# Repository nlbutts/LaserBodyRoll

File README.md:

# LaserBodyRoll

This product is designed to simulate wheel slip to prevent the front of a car from rising off the ground during hard acceleration. The device would be connected in between a wheel speed sensor and an engine ECU. Under normal conditions the device would pass through the wheel speed sensor directly to the engine ECU. If the front of the vehicle is detected rising off the ground, the system would increase the number of pulses per second (PPS) of the wheel to the engine ECU to simulate wheel slip. In theory, this should cause the engine ECU to reduce timing to prevent the simulated wheel slip and therefore reduce the front end from rising off the ground.
The system detects front end rise by using a laser rangefinder. The laser rangefinder can detect the small changes in distance from the mounting location to the ground. If the distance is increasing, then the system can increase the number of PPS from the wheel speed sensor to simulate the slip.

# Hardware Connections
A single cable gland will be used to bring signals into and out of the ECU enclosure.

ECU Connector

| Wire   | Description   |
| ------ | -----------   |
| Purple  | Power        |
| Black  | Ground        |
| Grey   | Analog Out 1  |
| Red    | Analog Out 2  |
| Brown  | DIN           |
| Orange | DOUT          |
| Yellow | CAN High      |
| Green  | CAN Low       |

The goal is to fit into this 

# Protocol between Processor and BLE
The PSoC and the Raspberry PI are connected via an SPI bus. The Pi is the SPI Master and the PSoC is a slave device. The packet that is transmitted to the PSOC is shown below

| Sync1 (8) | Sync2 (8) | Version (4)/Msg ID (4) | Length (8) | payload (2040) | CRC (8) |
| --------- | --------- | ---------------------- | ---------- | -------------- | ------- |
| 0x55      | 0xAA      | 0x01 / MSG ID          |            |                |         |

The number in parenthesis is how many bits are used for the various fields
The 4-bits of the version allows updates to the protocol. The 4-bits for the message ID allows
128 different message IDs. Length is the number of bytes in the payload 0-255 bytes.
The CRC is the CRC-8-CCITT using the following generator polynominal:
x^8 + x^2 + x + 1 (0x7)

| MSG ID | Description |
| ------ | ------------|
| 0      | Data input  |
| 1      | Data output |
| 2      | Main programming image |
| 3      | BLE programming image  |

Data input is a generic pass through message from the BLE interface to the main processor. The
data input is made up of an 8-bit UUID followed by the data item. Each data item has a unique
length, format, scale, etc. Data output is the same as data input, just going in the other
direction

| UUID | Description             | Size (bytes) | Data type | Units |
| ---- | ----------------------- | ------------ | --------- | ----- |
| 0    | Analog 1 slope          | 4            | float     | mm/mv |
| 1    | Analog 1 y offset       | 4            | float     | mv    |
| 2    | Analog 2 slope          | 4            | float     | mm/mv |
| 3    | Analog 2 y offset       | 4            | float     | mv    |
| 4    | Open drain pull up enbl | 1            | uint8     | bool  |
| 5    | Laser distance in mm    | 2            | uint16    | mm    |
| 6    | Accel X in mg           | 2            | uint16    | mg    |
| 7    | Accel Y in mg           | 2            | uint16    | mg    |
| 8    | Accel Z in mg           | 2            | uint16    | mg    |
| 9    | Gyro X in dps           | 2            | uint16    | dps   |
| 10   | Gyro Y in dps           | 2            | uint16    | dps   |
| 11   | Gyro Z in dps           | 2            | uint16    | dps   |
| 12   | Auto level gain         | 4            | float     |       |
| 13   | EPOCH time              | 4            | uint32    | epoch |
| 14   | Super cap voltage       | 2            | uint32    | mv    |

The main programming image is a LZMA compressed binary file. The BLE programming
image is an LZMA compressed cyacd file. Each BLE packet is only 23 bytes or so.
The programming images are transmitted with a byte counter as the first byte
of the payload. This allows a check that a packet hasn't been dropped and they are being
received in the correct order.

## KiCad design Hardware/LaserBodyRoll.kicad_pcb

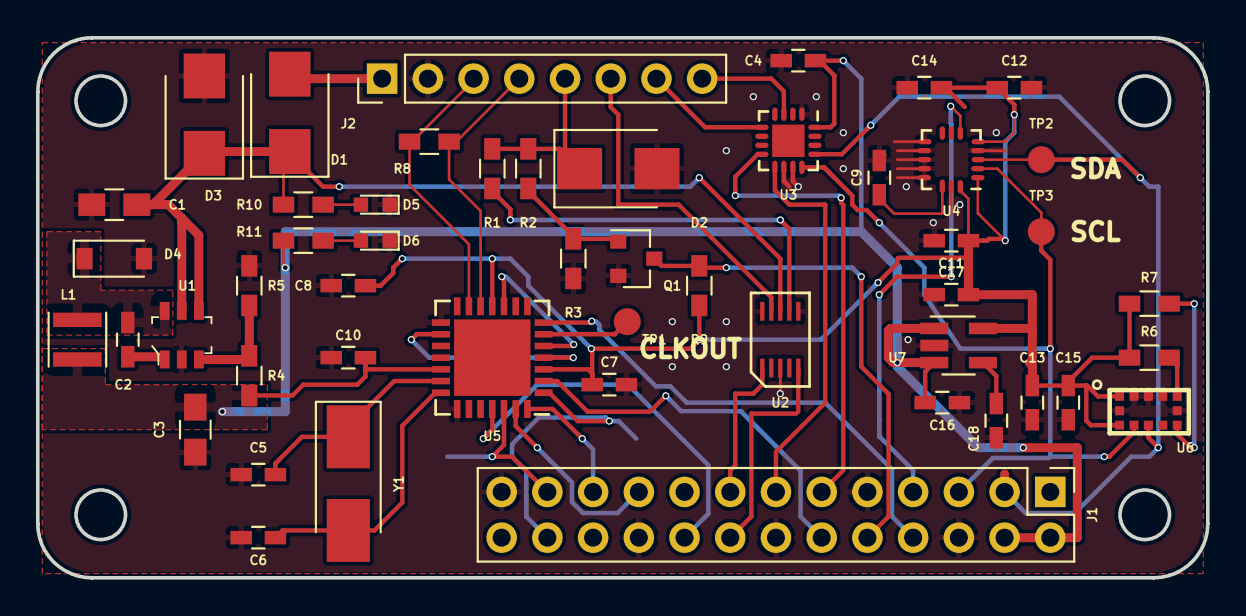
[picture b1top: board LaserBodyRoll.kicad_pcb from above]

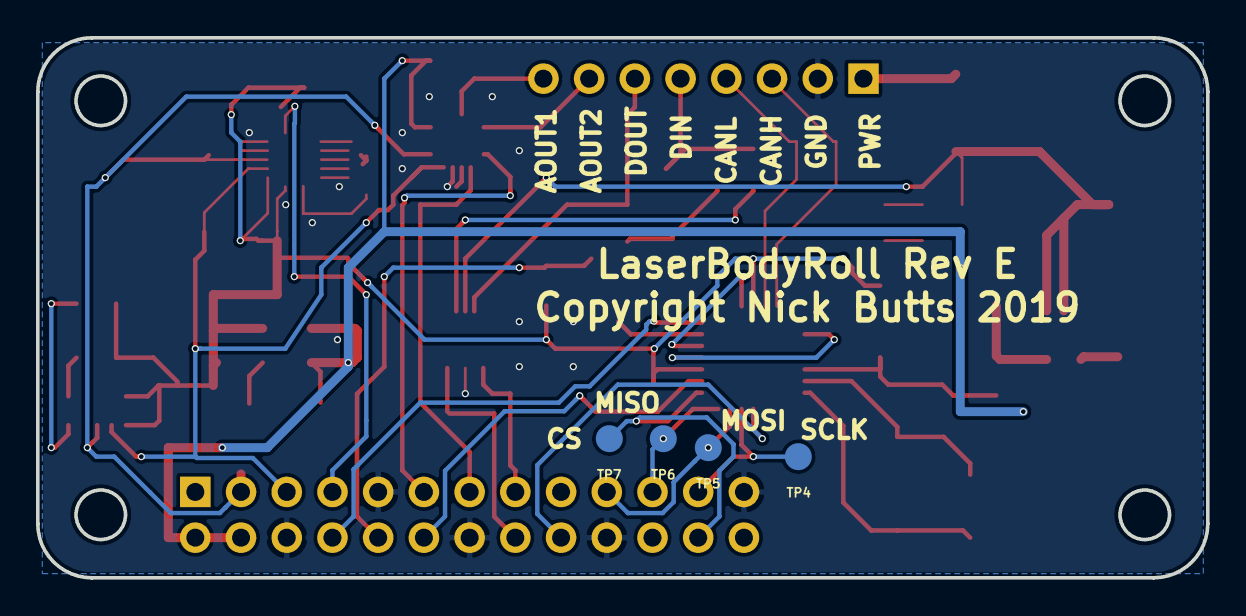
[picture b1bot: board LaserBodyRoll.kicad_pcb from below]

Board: 2 copper layers, 65.0 x 30.0 mm, 54 parts (4 on the bottom side), 42 nets.

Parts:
C1, C3: 10u; C_0805_HandSoldering
C2, C14: 10n; C_0603_HandSoldering
C4, C7, C8, C9, C10, C11, C13, C16, C18: 0.1u; C_0603_HandSoldering
C5, C6: 22p; C_0603_HandSoldering
C12: 2.2U; C_0603_HandSoldering
C15: 4.7u; C_0603_HandSoldering
C17: 1u; C_0603_HandSoldering
D1: STPS2L40; D_SMB
D2, D3: D_TVS; D_SMB
D4: D_Schottky; D_SOD-123
D5, D6: LED; LED_0603
J1: Conn_02x13_Odd_Even; Pin_Header_Straight_2x13_Pitch2.54mm
J2: Conn_01x08; Pin_Header_Straight_1x08_Pitch2.54mm
L1: 4.7u; L_Taiyo-Yuden_MD-3030
Q1: Q_NPN_BCE; SOT-23
R1, R2, R3: 24.3k; R_0603_HandSoldering
R4: 49.9k; R_0603_HandSoldering
R5: 9.53k; R_0603_HandSoldering
R6, R7: 10k; R_0603_HandSoldering
R8: 120; R_0603_HandSoldering
R9: 1k; R_0603_HandSoldering
R10: 600; R_0603_HandSoldering
R11: 250; R_0603_HandSoldering
TP1, TP2, TP3, TP4, TP5, TP6, TP7: TestPoint; Measurement_Point_Round-SMD-Pad_Small
U1: AOZ1280CI; SOT-23-6
U2: ITS42K5D; PG-TSON-10
U3: MCP47X; QFN-16-1EP_3x3mm_Pitch0.5mm
U4: ICM-20602; QFN-16-no_center_3x3mm_Pitch0.5mm
U5: MCP25625; QFN-28-1EP_6x6mm_Pitch0.65mm
U6: VL53L0X; VL53L0x
U7: LD3985; SOT-23-5_HandSoldering
Y1: 16MHz; Crystal_SMD_5032-2pin_5.0x3.2mm_HandSoldering

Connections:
12V: C1.1, D1.1, D3.1, R10.1, U1.4, U1.5, U2.8
+5V: C3.1, C4.1, C10.2, C16.2, J1.2, J1.4, L1.2, R4.1, R11.1, U3.16, U5.19, U7.1, U7.3
/12V_PULLUP: R1.2, U2.7
/ANA_OUT1: J2.8, U3.3
/ANA_OUT2: J2.7, U3.5
/CANH: J2.3, R8.1, U5.13
/CANL: J2.4, R8.2, U5.12
/DIN: D2.1, J2.5, R1.1, R2.1
/DOUT: J2.6, U2.9
/VL53L0X_GP: R7.2, U6.7
/VL53L0X_XSHUT: R6.2, U6.5
BCM4: J1.7, U4.6
BCM14: J1.8, U5.7
BCM15: J1.10, Q1.3, R9.2
BCM17: J1.11, U3.8
BCM18: J1.12, U5.2
BCM22: J1.15, U2.1
BCM23: J1.16, U2.5
BCM24: J1.18, U5.25
BCM27: J1.13, U3.9
GND: C1.2, C3.2, C4.2, C5.2, C6.2, C7.2, C8.2, C9.2, C10.1, C11.2, C12.2, C13.2, C14.2, C15.2, C16.1, C17.1, C18.1, D2.2, D3.2, D4.2, D5.1, D6.1, J1.6, J1.9, J1.14, J1.20, J1.25, J2.2, Q1.2, R3.2, R5.2, U1.2, U2.3, U2.6, U2.10, U3.1, U3.10, U3.11, U4.4, U4.9, U4.10, U4.11, U4.12, U4.13, U4.15, U5.15, U5.18, U5.22, U6.2, U6.3, U6.4, U6.6, U6.12, U7.2
unnamed: C2.1, D4.1, L1.1, U1.6
unnamed: C2.2, U1.1
unnamed: C5.1, U5.20, Y1.1
unnamed: C6.1, U5.21, Y1.2
unnamed: C9.1, U4.14
unnamed: C18.2, U7.4
unnamed: D5.2, R10.2
unnamed: D6.2, R11.2
unnamed: Q1.1, R2.2, R3.1
unnamed: R4.2, R5.1, U1.3
unnamed: TP1.1, U5.6
unnamed: U5.5, U5.10
unnamed: U5.4, U5.16
PI_CLK: J1.23, TP4.1, U5.26
PI_MISO: J1.21, TP6.1, U5.28
PI_MOSI: J1.19, TP5.1, U5.27
PI_NSS: J1.24, TP7.1, U5.1
SCL: J1.5, TP3.1, U3.12, U4.2, U6.10
SDA: J1.3, TP2.1, U3.13, U4.3, U6.9
VCC: C7.1, C8.1, C11.1, C12.1, C13.1, C14.1, C15.1, C17.2, R6.1, R7.1, R9.1, U4.1, U4.5, U4.16, U5.3, U5.11, U6.1, U6.11, U7.5
VIN: D1.2, J2.1

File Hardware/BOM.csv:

Source:,C:\projects\LaserBodyRoll\Hardware\LaserBodyRoll.sch,,,,,,,,,,,,,,,,
Date:,3/24/2019 14:10,,,,,,,,,,,,,,,,
Tool:,Eeschema (5.1.0)-1,,,,,,,,,,,,,,,,
Generator:,C:\Program Files\KiCad\bin\scripting\plugins/bom_csv_grouped_by_value.py,,,,,,,,,,,,,,,,
Component Count:,42,,,,,,,,,,,,,,,,
,,,,,,,,,,,,,,,,,
Individual Components:,,,,,,,,,,,,,,,,,
,,,,,,,,,,,,,,,,,
Item,Qty,Reference(s),Value,LibPart,Footprint,Datasheet,Category,DK_Datasheet_Link,DK_Detail_Page,Description,Digi-Key_PN,Digikey,Family,MPN,Manufacturer,Partnum,Status
,,C1,10u,Device:C,Capacitors_SMD:C_0805_HandSoldering,,,,,,,490-5523-1-ND,,,,GRM21BR61E106KA73L,
,,C2,10n,Device:C,Capacitors_SMD:C_0603_HandSoldering,,,,,,,399-1092-1-ND,,,,C0603C103J5RACTU,
,,C3,10u,Device:C,Capacitors_SMD:C_0805_HandSoldering,,,,,,,490-5523-1-ND,,,,GRM21BR61E106KA73L,
,,C4,0.1u,Device:C,Capacitors_SMD:C_0603_HandSoldering,~,,,,,,,,,,,
,,C5,22p,Device:C,Capacitors_SMD:C_0603_HandSoldering,~,,,,,,,,,,,
,,C6,22p,Device:C,Capacitors_SMD:C_0603_HandSoldering,~,,,,,,,,,,,
,,C7,0.1u,Device:C,Capacitors_SMD:C_0603_HandSoldering,~,,,,,,,,,,,
,,C8,0.1u,Device:C,Capacitors_SMD:C_0603_HandSoldering,~,,,,,,,,,,,
,,C9,0.1u,Device:C,Capacitors_SMD:C_0603_HandSoldering,,,,,,,,,,,,
,,C10,0.1u,Device:C,Capacitors_SMD:C_0603_HandSoldering,~,,,,,,,,,,,
,,C11,0.1u,Device:C,Capacitors_SMD:C_0603_HandSoldering,,,,,,,,,,,,
,,C12,2.2U,Device:C,Capacitors_SMD:C_0603_HandSoldering,,,,,,,,,,,,
,,C13,0.1u,Device:C,Capacitors_SMD:C_0603_HandSoldering,,,,,,,,,,,,
,,C14,10n,Device:C,Capacitors_SMD:C_0603_HandSoldering,,,,,,,,,,,,
,,C15,4.7u,Device:C,Capacitors_SMD:C_0603_HandSoldering,,,,,,,,,,,,
,,C16,0.1u,Device:C,Capacitors_SMD:C_0603_HandSoldering,~,,,,,,,,,,,
,,C17,0.1u,Device:C,Capacitors_SMD:C_0603_HandSoldering,~,,,,,,,,,,,
,,D1,STPS2L40,Device:D,Diodes_SMD:D_SMB,,,,,,,497-5574-1-ND,,,,STPS2L40U,
,,D2,D_TVS,Device:D_TVS,Diodes_SMD:D_SMB,,,,,,,732-9779-1-ND,,,,824520201,
,,D3,D_TVS,Device:D_TVS,Diodes_SMD:D_SMB,,,,,,,732-9779-1-ND,,,,824520201,
,,D4,D_Schottky,Device:D_Schottky,Diodes_SMD:D_SOD-123,,,,,,,B0540W-FDICT-ND,,,,B0540W-7-F,
,,J1,Conn_02x13_Odd_Even,Connector_Generic:Conn_02x13_Odd_Even,Pin_Headers:Pin_Header_Straight_2x13_Pitch2.54mm,~,,,,,,,,,,,
,,J2,Conn_01x08,Connector_Generic:Conn_01x08,Pin_Headers:Pin_Header_Straight_1x08_Pitch2.54mm,~,,,,,,,,,,,
,,L1,4.7u,Device:L,Inductors_SMD:L_Taiyo-Yuden_MD-3030,,,,,,,490-15954-1-ND,,,,LQH3NPN4R7MMEL,
,,Q1,Q_NPN_BCE,Device:Q_NPN_BCE,TO_SOT_Packages_SMD:SOT-23,,,,,,,MMBT3904FSCT-ND,,,,,
,,R1,24.3k,Device:R,Resistors_SMD:R_0603_HandSoldering,,,,,,,,,,,,
,,R2,24.3k,Device:R,Resistors_SMD:R_0603_HandSoldering,,,,,,,,,,,,
,,R3,24.3k,Device:R,Resistors_SMD:R_0603_HandSoldering,,,,,,,,,,,,
,,R4,49.9k,Device:R,Resistors_SMD:R_0603_HandSoldering,,,,,,,,,,,,
,,R5,9.53k,Device:R,Resistors_SMD:R_0603_HandSoldering,,,,,,,,,,,,
,,R6,10k,Device:R,Resistors_SMD:R_0603_HandSoldering,,,,,,,,,,,,
,,R7,10k,Device:R,Resistors_SMD:R_0603_HandSoldering,,,,,,,,,,,,
,,R8,120,Device:R,Resistors_SMD:R_0603_HandSoldering,~,,,,,,,,,,,
,,R9,1k,Device:R,Resistors_SMD:R_0603_HandSoldering,~,,,,,,,,,,,
,,U1,AOZ1280CI,dk_PMIC-Voltage-Regulators-DC-DC-Switching-Regulators:AOZ1280CI,digikey-footprints:SOT-23-6,http://aosmd.com/res/data_sheets/AOZ1280CI.pdf,Integrated Circuits (ICs),http://aosmd.com/res/data_sheets/AOZ1280CI.pdf,/product-detail/en/alpha-omega-semiconductor-inc/AOZ1280CI/785-1277-1-ND/2769845,IC REG BUCK ADJ 1.2A SOT23-6,785-1277-1-ND,,PMIC - Voltage Regulators - DC DC Switching Regulators,AOZ1280CI,Alpha & Omega Semiconductor Inc.,,Active
,,U2,ITS42K5D,General:ITS42K5D,KicadFootprint:PG-TSON-10,,,,,,,ITS42K5DLDFXUMA1CT-ND,,,,ITS42K5DLDFXUMA1,
,,U3,MCP47X,General:MCP47X,Housings_DFN_QFN:QFN-16-1EP_3x3mm_Pitch0.5mm,,,,,,,MCP47CVB22-E/MG-ND,,,,,
,,U4,ICM-20602,General:ICM-20602,Housings_DFN_QFN:QFN-16-1EP_3x3mm_Pitch0.5mm,,,,,,,1428-1060-1-ND,,,,ICM-20602,
,,U5,MCP25625,General:MCP25625,Housings_DFN_QFN:QFN-28-1EP_6x6mm_Pitch0.65mm,,,,,,,MCP25625T-E/MLCT-ND,,,,,
,,U6,VL53L0X,General:VL53L0X,KicadFootprint:VL53L0x,,,,,,,"	497-16538-1-ND",,,,VL53L0CXV0DH/1,
,,U7,LD3985,General:LD3985,TO_SOT_Packages_SMD:SOT-23-5_HandSoldering,,,,,,,497-3504-1-ND,,,,,
,,Y1,16MHz,Device:Crystal,Crystals:Crystal_SMD_5032-2pin_5.0x3.2mm_HandSoldering,~,,,,,,,,,,,
,,,,,,,,,,,,,,,,,
,,,,,,,,,,,,,,,,,
,,,,,,,,,,,,,,,,,
Collated Components:,,,,,,,,,,,,,,,,,
,,,,,,,,,,,,,,,,,
Item,Qty,Reference(s),Value,LibPart,Footprint,Datasheet,Category,DK_Datasheet_Link,DK_Detail_Page,Description,Digi-Key_PN,Digikey,Family,MPN,Manufacturer,Partnum,Status
1,2,"C1, C3",10u,Device:C,Capacitors_SMD:C_0805_HandSoldering,,,,,,,490-5523-1-ND,,,,GRM21BR61E106KA73L,
2,2,"C2, C14",10n,Device:C,Capacitors_SMD:C_0603_HandSoldering,,,,,,,399-1092-1-ND,,,,C0603C103J5RACTU,
3,9,"C4, C7, C8, C9, C10, C11, C13, C16, C17",0.1u,Device:C,Capacitors_SMD:C_0603_HandSoldering,~,,,,,,,,,,,
4,2,"C5, C6",22p,Device:C,Capacitors_SMD:C_0603_HandSoldering,~,,,,,,,,,,,
5,1,C12,2.2U,Device:C,Capacitors_SMD:C_0603_HandSoldering,,,,,,,,,,,,
6,1,C15,4.7u,Device:C,Capacitors_SMD:C_0603_HandSoldering,,,,,,,,,,,,
7,1,D1,STPS2L40,Device:D,Diodes_SMD:D_SMB,,,,,,,497-5574-1-ND,,,,STPS2L40U,
8,2,"D2, D3",D_TVS,Device:D_TVS,Diodes_SMD:D_SMB,,,,,,,732-9779-1-ND,,,,824520201,
9,1,D4,D_Schottky,Device:D_Schottky,Diodes_SMD:D_SOD-123,,,,,,,B0540W-FDICT-ND,,,,B0540W-7-F,
10,1,J1,Conn_02x13_Odd_Even,Connector_Generic:Conn_02x13_Odd_Even,Pin_Headers:Pin_Header_Straight_2x13_Pitch2.54mm,~,,,,,,,,,,,
11,1,J2,Conn_01x08,Connector_Generic:Conn_01x08,Pin_Headers:Pin_Header_Straight_1x08_Pitch2.54mm,~,,,,,,,,,,,
12,1,L1,4.7u,Device:L,Inductors_SMD:L_Taiyo-Yuden_MD-3030,,,,,,,490-15954-1-ND,,,,LQH3NPN4R7MMEL,
13,1,Q1,Q_NPN_BCE,Device:Q_NPN_BCE,TO_SOT_Packages_SMD:SOT-23,,,,,,,MMBT3904FSCT-ND,,,,,
14,3,"R1, R2, R3",24.3k,Device:R,Resistors_SMD:R_0603_HandSoldering,,,,,,,,,,,,
15,1,R4,49.9k,Device:R,Resistors_SMD:R_0603_HandSoldering,,,,,,,,,,,,
16,1,R5,9.53k,Device:R,Resistors_SMD:R_0603_HandSoldering,,,,,,,,,,,,
17,2,"R6, R7",10k,Device:R,Resistors_SMD:R_0603_HandSoldering,,,,,,,,,,,,
18,1,R8,120,Device:R,Resistors_SMD:R_0603_HandSoldering,~,,,,,,,,,,,
19,1,R9,1k,Device:R,Resistors_SMD:R_0603_HandSoldering,~,,,,,,,,,,,
20,1,U1,AOZ1280CI,dk_PMIC-Voltage-Regulators-DC-DC-Switching-Regulators:AOZ1280CI,digikey-footprints:SOT-23-6,http://aosmd.com/res/data_sheets/AOZ1280CI.pdf,Integrated Circuits (ICs),http://aosmd.com/res/data_sheets/AOZ1280CI.pdf,/product-detail/en/alpha-omega-semiconductor-inc/AOZ1280CI/785-1277-1-ND/2769845,IC REG BUCK ADJ 1.2A SOT23-6,785-1277-1-ND,,PMIC - Voltage Regulators - DC DC Switching Regulators,AOZ1280CI,Alpha & Omega Semiconductor Inc.,,Active
21,1,U2,ITS42K5D,General:ITS42K5D,KicadFootprint:PG-TSON-10,,,,,,,ITS42K5DLDFXUMA1CT-ND,,,,ITS42K5DLDFXUMA1,
22,1,U3,MCP47X,General:MCP47X,Housings_DFN_QFN:QFN-16-1EP_3x3mm_Pitch0.5mm,,,,,,,MCP47CVB22-E/MG-ND,,,,,
23,1,U4,ICM-20602,General:ICM-20602,Housings_DFN_QFN:QFN-16-1EP_3x3mm_Pitch0.5mm,,,,,,,1428-1060-1-ND,,,,ICM-20602,
24,1,U5,MCP25625,General:MCP25625,Housings_DFN_QFN:QFN-28-1EP_6x6mm_Pitch0.65mm,,,,,,,MCP25625T-E/MLCT-ND,,,,,
25,1,U6,VL53L0X,General:VL53L0X,KicadFootprint:VL53L0x,,,,,,,"	497-16538-1-ND",,,,VL53L0CXV0DH/1,
26,1,U7,LD3985,General:LD3985,TO_SOT_Packages_SMD:SOT-23-5_HandSoldering,,,,,,,497-3504-1-ND,,,,,
27,1,Y1,16MHz,Device:Crystal,Crystals:Crystal_SMD_5032-2pin_5.0x3.2mm_HandSoldering,~,,,,,,,,,,,

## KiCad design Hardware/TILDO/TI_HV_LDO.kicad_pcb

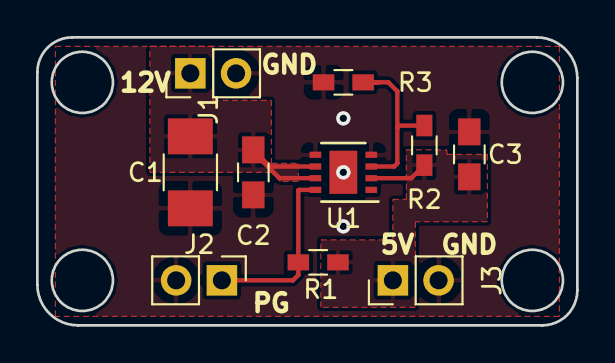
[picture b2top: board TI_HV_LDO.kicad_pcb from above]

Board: 2 copper layers, 30.0 x 16.0 mm, 10 parts (0 on the bottom side), 5 nets.

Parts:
C1: 22u; C_1210_HandSoldering
C2, C3: 10u; C_0805_HandSoldering
J1, J2, J3: Conn_01x02; Pin_Header_Straight_1x02_Pitch2.54mm
R1, R3: 10k; R_0603_HandSoldering
R2: 30k; R_0603_HandSoldering
U1: TPS7A19; DFN-8-1EP_3x3mm_Pitch0.65mm

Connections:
GND: C1.2, C2.2, C3.2, J1.2, J2.2, J3.2, R3.2, U1.4, U1.5, U1.9
unnamed: C1.1, C2.1, J1.1, U1.6, U1.7
unnamed: C3.1, J3.1, R1.2, R2.1, U1.2
unnamed: J2.1, R1.1, U1.8
unnamed: R2.2, R3.1, U1.3

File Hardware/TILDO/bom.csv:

"Source:","C:\projects\LaserBodyRoll\Hardware\TILDO\TI_HV_LDO.sch"
"Date:","6/24/2018 4:46:14 PM"
"Tool:","Eeschema (2017-09-19 revision dddaa7e69)-makepkg"
"Generator:","bom_csv_grouped_by_value.py"
"Component Count:","10"

"Individual Components:"

"Item","Qty","Reference(s)","Value","LibPart","Footprint","Datasheet"
"","","C1","22u","device:C","Capacitors_SMD:C_1210_HandSoldering",""
"","","C2","10u","device:C","Capacitors_SMD:C_0805_HandSoldering",""
"","","C3","10u","device:C","Capacitors_SMD:C_0805_HandSoldering",""
"","","J1","Conn_01x02","conn:Conn_01x02","Pin_Headers:Pin_Header_Straight_1x02_Pitch2.54mm",""
"","","J2","Conn_01x02","conn:Conn_01x02","Pin_Headers:Pin_Header_Straight_1x02_Pitch2.54mm",""
"","","J3","Conn_01x02","conn:Conn_01x02","Pin_Headers:Pin_Header_Straight_1x02_Pitch2.54mm",""
"","","R1","10k","device:R","Resistors_SMD:R_0603_HandSoldering",""
"","","R2","30k","device:R","Resistors_SMD:R_0603_HandSoldering",""
"","","R3","10k","device:R","Resistors_SMD:R_0603_HandSoldering",""
"","","U1","TPS7A19","General:TPS7A19","Housings_DFN_QFN:DFN-8-1EP_3x3mm_Pitch0.65mm",""



"Collated Components:"

"Item","Qty","Reference(s)","Value","LibPart","Footprint","Datasheet"
"1","1","C1","22u","device:C","Capacitors_SMD:C_1210_HandSoldering",""
"2","2","C2, C3","10u","device:C","Capacitors_SMD:C_0805_HandSoldering",""
"3","3","J1, J2, J3","Conn_01x02","conn:Conn_01x02","Pin_Headers:Pin_Header_Straight_1x02_Pitch2.54mm",""
"4","2","R1, R3","10k","device:R","Resistors_SMD:R_0603_HandSoldering",""
"5","1","R2","30k","device:R","Resistors_SMD:R_0603_HandSoldering",""
"6","1","U1","TPS7A19","General:TPS7A19","Housings_DFN_QFN:DFN-8-1EP_3x3mm_Pitch0.65mm",""

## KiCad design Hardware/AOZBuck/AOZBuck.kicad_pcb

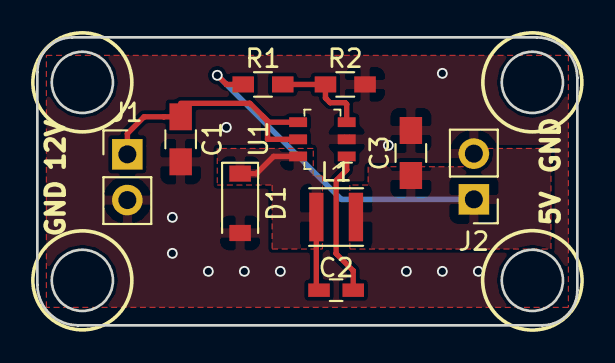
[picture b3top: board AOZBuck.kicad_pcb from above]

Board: 2 copper layers, 30.0 x 16.0 mm, 10 parts (0 on the bottom side), 6 nets.

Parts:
C1, C3: 10u; C_0805_HandSoldering
C2: 10n; C_0603_HandSoldering
D1: D_Schottky; D_SOD-123
J1, J2: Conn_01x02; Pin_Header_Straight_1x02_Pitch2.54mm
L1: 4.7u; L_Taiyo-Yuden_MD-3030
R1: 49.9k; R_0603_HandSoldering
R2: 9.53k; R_0603_HandSoldering
U1: AOZ1280CI; SOT-23-6

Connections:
GND: C1.2, C3.2, D1.2, J1.2, J2.2, R2.2, U1.2
unnamed: C1.1, J1.1, U1.4, U1.5
unnamed: C2.1, D1.1, L1.1, U1.6
unnamed: C2.2, U1.1
unnamed: C3.1, J2.1, L1.2, R1.1
unnamed: R1.2, R2.1, U1.3

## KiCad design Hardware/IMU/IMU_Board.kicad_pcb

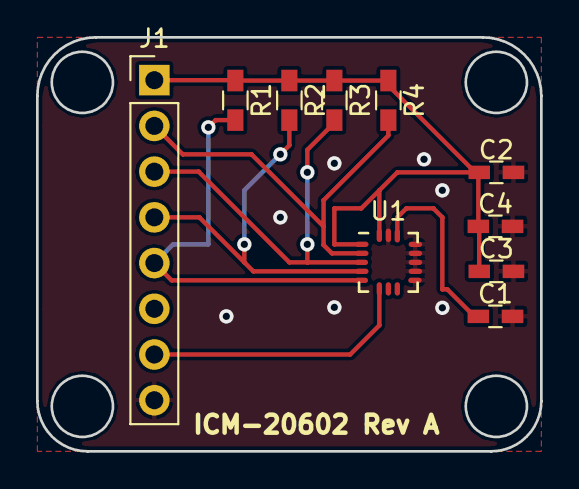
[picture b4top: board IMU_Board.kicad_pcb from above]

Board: 2 copper layers, 28.0 x 23.0 mm, 10 parts (0 on the bottom side), 8 nets.

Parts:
C1, C2: 0.1u; C_0603_HandSoldering
C3: 2.2U; C_0603_HandSoldering
C4: 10n; C_0603_HandSoldering
J1: Conn_01x08; Pin_Header_Straight_1x08_Pitch2.54mm
R1, R2, R3, R4: 10K; R_0603_HandSoldering
U1: ICM-20602; QFN-16-no_center_3x3mm_Pitch0.5mm

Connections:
GND: C1.2, C2.2, C3.2, C4.2, J1.8, U1.9, U1.10, U1.11, U1.12, U1.13, U1.15
unnamed: C1.1, U1.14
unnamed: J1.2, R4.2, U1.2
unnamed: J1.3, R3.2, U1.3
unnamed: J1.4, R2.2, U1.4
unnamed: J1.5, R1.2, U1.5
unnamed: J1.7, U1.6
VCC: C2.1, C3.1, C4.1, J1.1, R1.1, R2.1, R3.1, R4.1, U1.1, U1.16

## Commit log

2017-09-16 Checked in the documentation.
2017-10-18 Added the Hardware project.
2017-10-19 Updated.
2017-10-20 Added processor.
2017-10-22 Added software, several new pages to the schematic.
2017-10-23 Updated the schematic
2017-10-23 Deleted bak files.
2017-10-25 Updated the design and added schematics.
2017-10-25 Added software.
2017-10-25 Moved the PSoC project
2017-10-26 Working on footprints.
2017-10-27 Various updates.
2017-10-30 Assigned packages to all parts. Starting layout
2017-11-01 Added a mechanical directory. The design is WAY to large to fit on the same form factor as a Pi zero.
2017-11-09 Updated foot prints.
2017-11-09 Started to place parts.
2017-11-09 Added the tps datasheet.
2017-11-17 Worked on placement.
2017-11-20 Updated the board outline and placement of parts.
2017-11-22 Working on the routing.
2017-11-24 Partial routing, but it is starting to look weird. I'm going to try and change the pinout of the PSoC to make routing easier.
2017-11-24 The board is routed. Not the best routing job, but it should work.
2017-11-27 Added box and pi outlines.
2017-12-03 Updated part numbers
2017-12-28 Totally f&^% up the board. This is my attempt to fix all of those issues.
2018-01-02 Updated the gerber output settings.
2018-01-20 Restarted the Analog Coproc project to only use PSoC Creator 4.1
2018-01-21 Redid the PSoC software in 4.1.
2018-01-21 Added SPI for testing with the Pi
2018-01-21 Added Pi python code
2018-01-21 Added a script to mount the pi smb share for sublime.
2018-01-21 Checked in the first version of a PSoC python library.
2018-01-21 Minor update to support the SPI interface testing.
2018-01-24 Added the start of the UI.
2018-01-26 Tweaked more UI settings. Have a simple web form working.
2018-01-27 Updated the readme file.
2018-01-27 Added the protocol code to the PSoC.
2018-01-27 Updated the PSoC protocol.
2018-01-27 Updated the Pi Python code to talk to the PSoC.
2018-01-28 Added a JS code that will periodically refresh from a URL
2018-01-28 Checked in the PiFinder code and updated it to talk to Python.
2018-02-01 Updated the readme, working on a new protocol.
2018-02-01 Updated the protocol.
2018-02-02 Fixed the status protocol to/from the psoc.
2018-02-03 Big refactor to organize this project.
2018-02-03 Initial version of the reprogramming app. It compiles and runs, now just need to connect up the SPI bus.
2018-02-04 REPROGRAMMING WORKSgit statusgit status!
2018-02-04 Added the analog_laser project.
2018-02-10 Added a bootloader for the PSoC
2018-02-11 Refactored the entire design. The schematic has all of the components.
2018-02-11 Added the BLE PSoC design.
2018-02-11 Worked on initial placement.
2018-02-12 Removed a bunch of old files. Created a board outline based on the Bud Box PN-1321-CMB
2018-02-14 Added a script to calculate current and charge time of the supercap.
2018-02-18 Finished board. Added lots of stiching vias after reading a TI app note on EMC.
2018-02-18 Added a resistor for the CAN phy lines. Added test points for SPI lines.
2018-02-18 Routed test points
2018-03-01 Order this version of the board.
2018-03-08 Fixed some pads.
2018-03-08 Checked in the ST cube output and the toolchain.
2018-03-11 Have a working project that blinks LEDs.
2018-03-11 Major rework. Trying to get interrupts working.
2018-03-12 More tweaking. I have the timers system working, but they are about 10 times too fast.
2018-03-12 Tweaks to the BLE module to get it to work.
2018-03-14 Got the TIM2 clock working. It appartently ignores the prescaler. It looks like an errata, but it is not documented as such.
2018-03-16 Fixed really stupid bugs in STs code.
2018-03-16 Updated linker stuff to make the application much much smaller. The code is now down to 14132 bytes.
2018-03-16 Added fwimages and updater app.
2018-03-19 Added the library for the VL53L0X sensor.
2018-03-23 Updates to prevent compiler warnings. Tested the Flash and that appears to work. The IMU and the Laser rangefinder are not working. Most likely not solder correctly.
2018-03-25 Everything appears to work except the IMU. I've tried to switch to I2C and I still can't talk to the part. I'm going to move on without the IMU.
2018-03-27 Added more code. Need to abstract the SPI interface.
2018-03-28 Have the first version of the SPI and NORFlash modules working.
2018-03-30 Added the AOZBuck board.
2018-03-31 The NOR Flash is working.
2018-04-01 NVSections are now working. Added some unit tests to verify the operation.
2018-04-02 Updated Buck layout.
2018-04-04 Created a small buck and LDO board.
2018-04-04 Add some silkscreen items
2018-04-04 More updates before ordering.
2018-04-06 Checked in some new power boards and a stand alone IMU board.
2018-04-06 Working on the BLE protocol.
2018-04-18 Updated the architecture.
2018-04-18 Updated the readme file with the BLE protocol.
2018-07-26 Added a bunch of the mechanical designs.
2019-01-20 Unit test is passing for the BLE/Main processing comm system.
2019-01-20 Having issues with the libcrc showing up in git.
2019-01-20 Checked in libcrc
2019-01-20 Removed the motion driver code.
2019-01-20 Added the hardware design info.
2019-01-20 Attempting to transmit the first message to the BLE module.
2019-01-21 Updated the BLE app. It blinks an LED at 1 Hz at the moment.
2019-02-09 SPI interface is transmitting the ble_protocol messages.
2019-02-09 Added some libraries and mechanical drawings for the box.
2019-02-09 Added a system BOM
2019-02-17 Working on a redesigned board.
2019-02-17 Big refactor, got rid of all software. Everything will run on the Pi.
2019-02-18 Added an LDO to power this board.
2019-03-29 Added rescued parts.
2019-03-29 Saved the schematic.
2019-03-31 Added python test scripts for the hardware.
2019-03-31 Updated the test_can library.
2019-04-06 Moved the CAN and DAC into classes. The IO is basic enough that it doesn't need a class.
2019-04-07 Added the icm20602 code and some test code. It keeps timing out via I2C.
2019-04-12 Added the rescue backend stuff.
2019-04-12 Deleted the lava code base.
2019-04-12 Checked the python code into the branch.
2019-04-18 Fixed problems on the board and added LEDs.
2019-05-19 Minor update to the icm20602 driver to generate 100 Hz data.

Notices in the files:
Hardware/LaserBodyRoll.kicad_pcb:
Copyright Nick Butts 2019
